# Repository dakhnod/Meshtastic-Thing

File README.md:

# Meshtastic-Thing

## Version 1/2

This board is a bit cleaner. It is composed of
- an esp32c3 super mini board
- an RFM95 board
- the PCB, as found in [the kicad folder](kicad/)

This PCB has two mino versions, with the second one labeled `v2`.
The first one connects `DIO0` with the ESP pin 8, which renders the built-in LED unusable.

The second version fixes this. Currently, the kicad Project contains the second version, but the variants.h file still uses GPIO8. You need to adjust this file if using the provided PCB.

Once I receive the second version and test it I will update this repository.

Steps:
1. Get an esp32c3 super mini board.
2. Get an RFM95 module
3. Solder up all boards as seen in the pictures
4. Clone the meshtastic firmware repo (recursively)
5. Open the repo firm VSCode with PlatformIO
6. Change out the file `variants/esp32c3/diy/esp32c3_super_mini/variant.h` to [the one](variants/esp32c3/diy/esp32c3_super_mini/variant.h) in this repo
7. If using the PCB from this repo, update the variants.h file to use pin 9 for DIO0
8. Build and flash the PlatformIO configuration `env:esp32c3_super_mini`
9. Check out [BLEnky](https://structure.nullco.de/?node_id=6622041d1a95fb4425f2323a&token=3c55f7bb1de0e79c9020dbb09deac741df56fc5474825407abb94f96714ce134) (unrelated, just wanted to advertise)
10. ???
11. Profit

## Version 0

Weird Meshtastic prototype I build.
For everyone wanting to replicate this (for reasons beyond me), here is some information.
Keep in mind that this instruction requires some skill level. If you have questions, open an issue!

Steps:
1. Get a Board like the one shown in the AliExpress listing (could also be black, doesn't matter. Open an issue if you're unsure)
2. Get an RFM95 module
3. Solder everything up according to the pictures (pin definition in [variant.h](variants/nrf52840/diy/nrf52_promicro_diy_xtal/variant.h))
4. Clone the meshtastic firmware repo (recursively)
5. Open the repo firm VSCode with PlatformIO
6. Change out the file `variants/nrf52840/diy/nrf52_promicro_diy_xtal/variant.h` to the one in this repo
7. Build and flash the PlatformIO configuration `env:nrf52_promicro_diy_xtal`
8. Check out [BLEnky](https://structure.nullco.de/?node_id=6622041d1a95fb4425f2323a&token=3c55f7bb1de0e79c9020dbb09deac741df56fc5474825407abb94f96714ce134) (unrelated, just wanted to advertise)
9. ???
10. Profit

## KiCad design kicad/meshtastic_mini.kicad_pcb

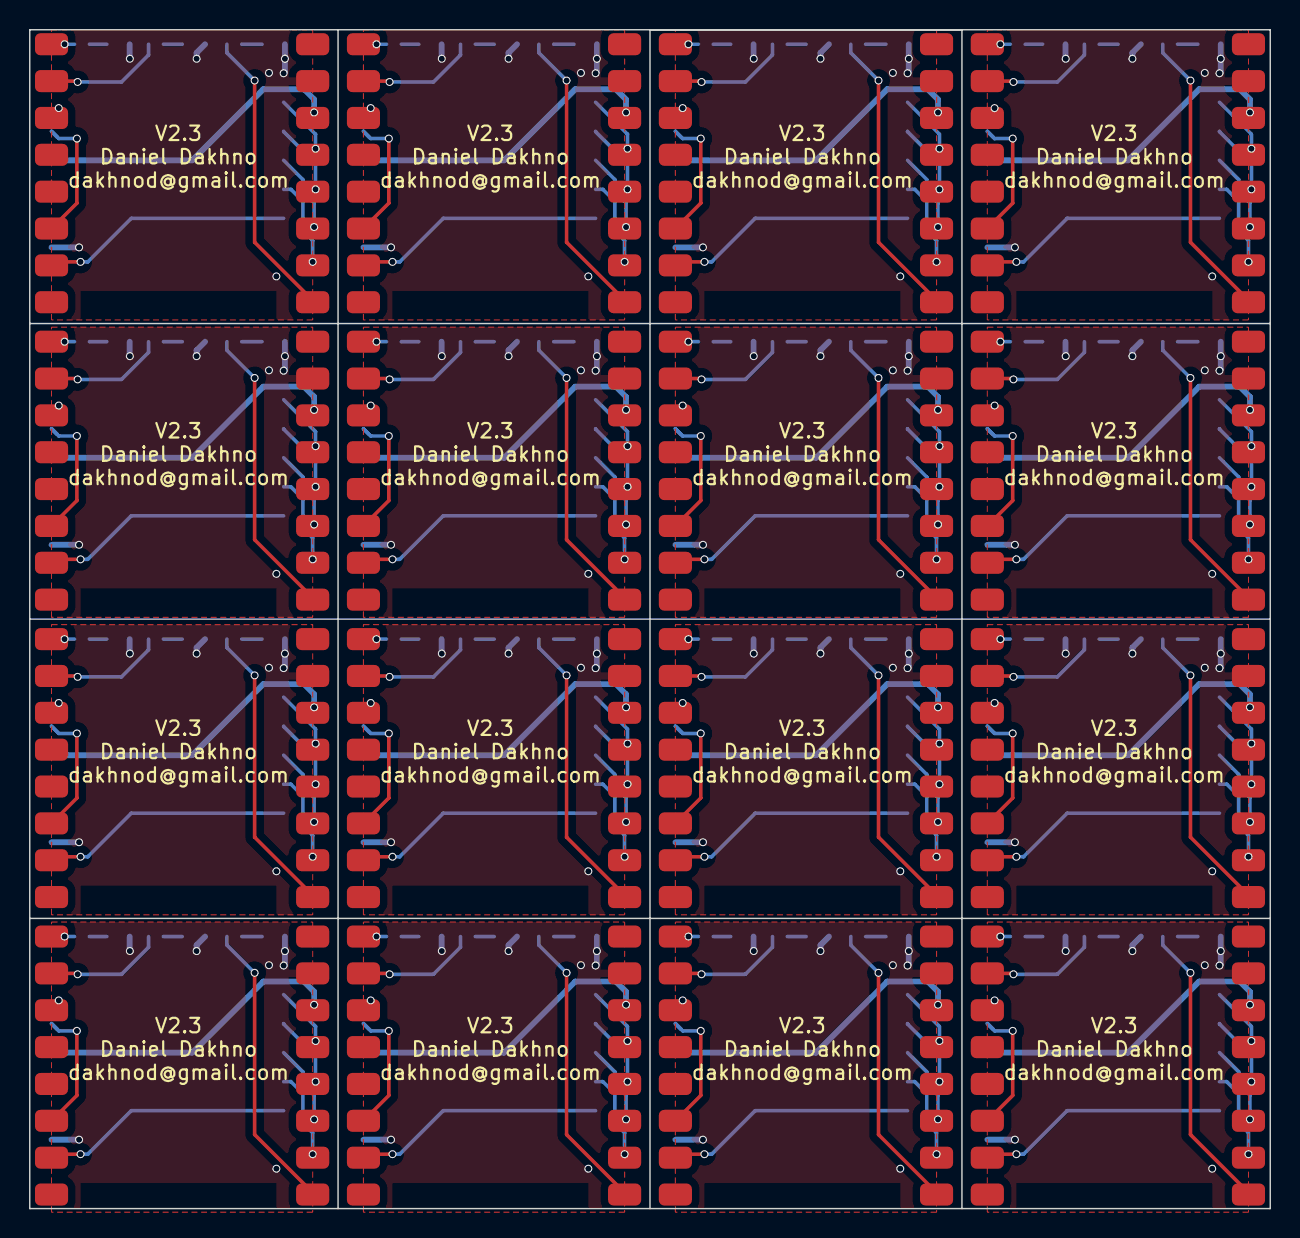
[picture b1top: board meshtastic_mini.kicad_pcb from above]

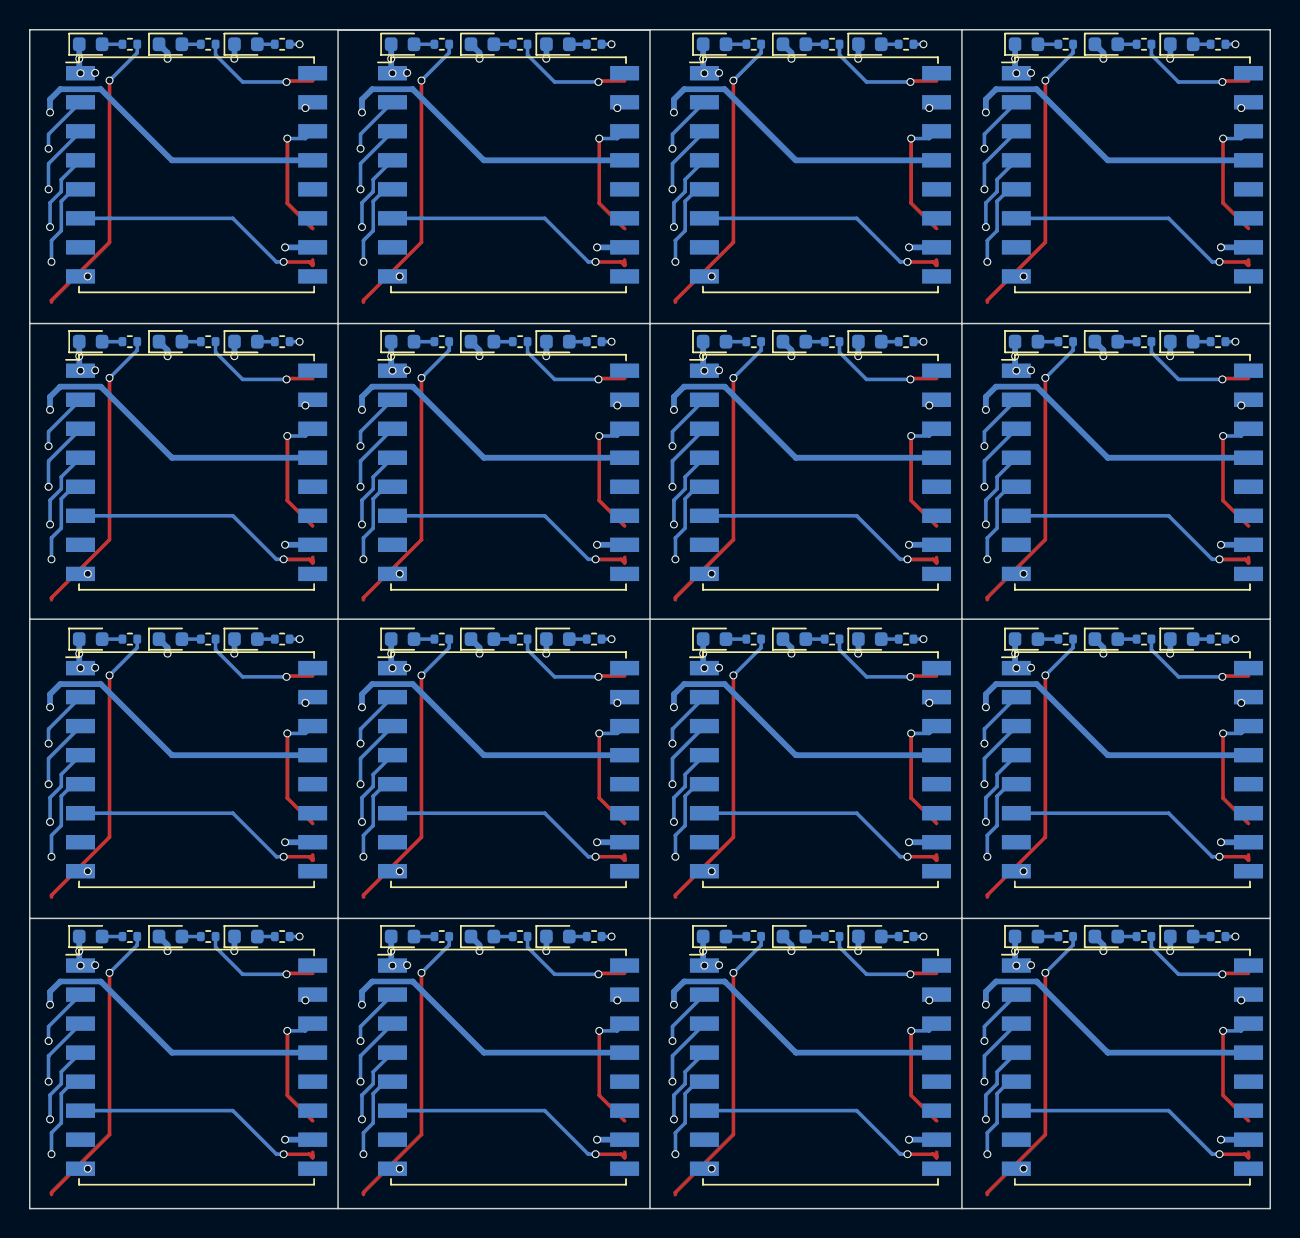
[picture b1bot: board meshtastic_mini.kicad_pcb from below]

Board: 2 copper layers, 85.5 x 81.2 mm, 128 parts (112 on the bottom side), 15 nets.

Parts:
D1, D2, D3, D4, D5, D6, D7, D8, D9, D10, D11, D12, D13, D14, D15, D16, D17, D18, D19, D20, D21, D22, D23, D24, D25, D26, D27, D28, D29, D30, D31, D32, D33, D34, D35, D36, D37, D38, D39, D40, D41, D42, D43, D44, D45, D46, D47, D48: LED; LED_0603_1608Metric
R1, R2, R3, R4, R5, R6, R7, R8, R9, R10, R11, R12, R13, R14, R15, R16, R17, R18, R19, R20, R21, R22, R23, R24, R25, R26, R27, R28, R29, R30, R31, R32, R33, R34, R35, R36, R37, R38, R39, R40, R41, R42, R43, R44, R45, R46, R47, R48: 1K; R_0402_1005Metric
U1, U3, U5, U7, U9, U11, U13, U15, U17, U19, U21, U23, U25, U27, U29, U31: ESP32-C3_SuperMini; ESP32-C3 SuperMini
U2, U4, U6, U8, U10, U12, U14, U16, U18, U20, U22, U24, U26, U28, U30, U32: RFM95W-868S2; HOPERF_RFM9XW_SMD

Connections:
+3.3V: U1.11 (3V3), U2.13 (3.3V), U3.11 (3V3), U4.13 (3.3V), U5.11 (3V3), U6.13 (3.3V), U7.11 (3V3), U8.13 (3.3V), U9.11 (3V3), U10.13 (3.3V), U11.11 (3V3), U12.13 (3.3V), U13.11 (3V3), U14.13 (3.3V), U15.11 (3V3), U16.13 (3.3V), U17.11 (3V3), U18.13 (3.3V), U19.11 (3V3), U20.13 (3.3V), U21.11 (3V3), U22.13 (3.3V), U23.11 (3V3), U24.13 (3.3V), U25.11 (3V3), U26.13 (3.3V), U27.11 (3V3), U28.13 (3.3V), U29.11 (3V3), U30.13 (3.3V), U31.11 (3V3), U32.13 (3.3V)
/DIO0: U1.6 (GPIO10), U2.14 (DIO0), U3.6 (GPIO10), U4.14 (DIO0), U5.6 (GPIO10), U6.14 (DIO0), U7.6 (GPIO10), U8.14 (DIO0), U9.6 (GPIO10), U10.14 (DIO0), U11.6 (GPIO10), U12.14 (DIO0), U13.6 (GPIO10), U14.14 (DIO0), U15.6 (GPIO10), U16.14 (DIO0), U17.6 (GPIO10), U18.14 (DIO0), U19.6 (GPIO10), U20.14 (DIO0), U21.6 (GPIO10), U22.14 (DIO0), U23.6 (GPIO10), U24.14 (DIO0), U25.6 (GPIO10), U26.14 (DIO0), U27.6 (GPIO10), U28.14 (DIO0), U29.6 (GPIO10), U30.14 (DIO0), U31.6 (GPIO10), U32.14 (DIO0)
/DIO1: U1.3 (GPIO7), U2.15 (DIO1), U3.3 (GPIO7), U4.15 (DIO1), U5.3 (GPIO7), U6.15 (DIO1), U7.3 (GPIO7), U8.15 (DIO1), U9.3 (GPIO7), U10.15 (DIO1), U11.3 (GPIO7), U12.15 (DIO1), U13.3 (GPIO7), U14.15 (DIO1), U15.3 (GPIO7), U16.15 (DIO1), U17.3 (GPIO7), U18.15 (DIO1), U19.3 (GPIO7), U20.15 (DIO1), U21.3 (GPIO7), U22.15 (DIO1), U23.3 (GPIO7), U24.15 (DIO1), U25.3 (GPIO7), U26.15 (DIO1), U27.3 (GPIO7), U28.15 (DIO1), U29.3 (GPIO7), U30.15 (DIO1), U31.3 (GPIO7), U32.15 (DIO1)
/RESET: U1.7 (GPIO20), U2.6 (RESET), U3.7 (GPIO20), U4.6 (RESET), U5.7 (GPIO20), U6.6 (RESET), U7.7 (GPIO20), U8.6 (RESET), U9.7 (GPIO20), U10.6 (RESET), U11.7 (GPIO20), U12.6 (RESET), U13.7 (GPIO20), U14.6 (RESET), U15.7 (GPIO20), U16.6 (RESET), U17.7 (GPIO20), U18.6 (RESET), U19.7 (GPIO20), U20.6 (RESET), U21.7 (GPIO20), U22.6 (RESET), U23.7 (GPIO20), U24.6 (RESET), U25.7 (GPIO20), U26.6 (RESET), U27.7 (GPIO20), U28.6 (RESET), U29.7 (GPIO20), U30.6 (RESET), U31.7 (GPIO20), U32.6 (RESET)
/SPI_MISO: U1.12 (GPIO4), U2.2 (MISO), U3.12 (GPIO4), U4.2 (MISO), U5.12 (GPIO4), U6.2 (MISO), U7.12 (GPIO4), U8.2 (MISO), U9.12 (GPIO4), U10.2 (MISO), U11.12 (GPIO4), U12.2 (MISO), U13.12 (GPIO4), U14.2 (MISO), U15.12 (GPIO4), U16.2 (MISO), U17.12 (GPIO4), U18.2 (MISO), U19.12 (GPIO4), U20.2 (MISO), U21.12 (GPIO4), U22.2 (MISO), U23.12 (GPIO4), U24.2 (MISO), U25.12 (GPIO4), U26.2 (MISO), U27.12 (GPIO4), U28.2 (MISO), U29.12 (GPIO4), U30.2 (MISO), U31.12 (GPIO4), U32.2 (MISO)
/SPI_MOSI: U1.13 (GPIO3), U2.3 (MOSI), U3.13 (GPIO3), U4.3 (MOSI), U5.13 (GPIO3), U6.3 (MOSI), U7.13 (GPIO3), U8.3 (MOSI), U9.13 (GPIO3), U10.3 (MOSI), U11.13 (GPIO3), U12.3 (MOSI), U13.13 (GPIO3), U14.3 (MOSI), U15.13 (GPIO3), U16.3 (MOSI), U17.13 (GPIO3), U18.3 (MOSI), U19.13 (GPIO3), U20.3 (MOSI), U21.13 (GPIO3), U22.3 (MOSI), U23.13 (GPIO3), U24.3 (MOSI), U25.13 (GPIO3), U26.3 (MOSI), U27.13 (GPIO3), U28.3 (MOSI), U29.13 (GPIO3), U30.3 (MOSI), U31.13 (GPIO3), U32.3 (MOSI)
/SPI_NSS: U1.15 (GPIO1), U2.5 (NSS), U3.15 (GPIO1), U4.5 (NSS), U5.15 (GPIO1), U6.5 (NSS), U7.15 (GPIO1), U8.5 (NSS), U9.15 (GPIO1), U10.5 (NSS), U11.15 (GPIO1), U12.5 (NSS), U13.15 (GPIO1), U14.5 (NSS), U15.15 (GPIO1), U16.5 (NSS), U17.15 (GPIO1), U18.5 (NSS), U19.15 (GPIO1), U20.5 (NSS), U21.15 (GPIO1), U22.5 (NSS), U23.15 (GPIO1), U24.5 (NSS), U25.15 (GPIO1), U26.5 (NSS), U27.15 (GPIO1), U28.5 (NSS), U29.15 (GPIO1), U30.5 (NSS), U31.15 (GPIO1), U32.5 (NSS)
/SPI_SCK: U1.14 (GPIO2), U2.4 (SCK), U3.14 (GPIO2), U4.4 (SCK), U5.14 (GPIO2), U6.4 (SCK), U7.14 (GPIO2), U8.4 (SCK), U9.14 (GPIO2), U10.4 (SCK), U11.14 (GPIO2), U12.4 (SCK), U13.14 (GPIO2), U14.4 (SCK), U15.14 (GPIO2), U16.4 (SCK), U17.14 (GPIO2), U18.4 (SCK), U19.14 (GPIO2), U20.4 (SCK), U21.14 (GPIO2), U22.4 (SCK), U23.14 (GPIO2), U24.4 (SCK), U25.14 (GPIO2), U26.4 (SCK), U27.14 (GPIO2), U28.4 (SCK), U29.14 (GPIO2), U30.4 (SCK), U31.14 (GPIO2), U32.4 (SCK)
GND: D1.1 (K), D2.1 (K), D3.1 (K), D4.1 (K), D5.1 (K), D6.1 (K), D7.1 (K), D8.1 (K), D9.1 (K), D10.1 (K), D11.1 (K), D12.1 (K), D13.1 (K), D14.1 (K), D15.1 (K), D16.1 (K), D17.1 (K), D18.1 (K), D19.1 (K), D20.1 (K), D21.1 (K), D22.1 (K), D23.1 (K), D24.1 (K), D25.1 (K), D26.1 (K), D27.1 (K), D28.1 (K), D29.1 (K), D30.1 (K), D31.1 (K), D32.1 (K), D33.1 (K), D34.1 (K), D35.1 (K), D36.1 (K), D37.1 (K), D38.1 (K), D39.1 (K), D40.1 (K), D41.1 (K), D42.1 (K), D43.1 (K), D44.1 (K), D45.1 (K), D46.1 (K), D47.1 (K), D48.1 (K), U1.10 (GND), U2.1 (GND), U2.8 (GND), U2.10 (GND), U3.10 (GND), U4.1 (GND), U4.8 (GND), U4.10 (GND), U5.10 (GND), U6.1 (GND), U6.8 (GND), U6.10 (GND), U7.10 (GND), U8.1 (GND), U8.8 (GND), U8.10 (GND), U9.10 (GND), U10.1 (GND), U10.8 (GND), U10.10 (GND), U11.10 (GND), U12.1 (GND), U12.8 (GND), U12.10 (GND), U13.10 (GND), U14.1 (GND), U14.8 (GND), U14.10 (GND), U15.10 (GND), U16.1 (GND), U16.8 (GND), U16.10 (GND), U17.10 (GND), U18.1 (GND), U18.8 (GND), U18.10 (GND), U19.10 (GND), U20.1 (GND), U20.8 (GND), U20.10 (GND), U21.10 (GND), U22.1 (GND), U22.8 (GND), U22.10 (GND), U23.10 (GND), U24.1 (GND), U24.8 (GND), U24.10 (GND), U25.10 (GND), U26.1 (GND), U26.8 (GND), U26.10 (GND), U27.10 (GND), U28.1 (GND), U28.8 (GND), U28.10 (GND), U29.10 (GND), U30.1 (GND), U30.8 (GND), U30.10 (GND), U31.10 (GND), U32.1 (GND), U32.8 (GND), U32.10 (GND)
unnamed: D1.2 (A), D4.2 (A), D7.2 (A), D10.2 (A), D13.2 (A), D16.2 (A), D19.2 (A), D22.2 (A), D25.2 (A), D28.2 (A), D31.2 (A), D34.2 (A), D37.2 (A), D40.2 (A), D43.2 (A), D46.2 (A), R1.2, R4.2, R7.2, R10.2, R13.2, R16.2, R19.2, R22.2, R25.2, R28.2, R31.2, R34.2, R37.2, R40.2, R43.2, R46.2
unnamed: D2.2 (A), D5.2 (A), D8.2 (A), D11.2 (A), D14.2 (A), D17.2 (A), D20.2 (A), D23.2 (A), D26.2 (A), D29.2 (A), D32.2 (A), D35.2 (A), D38.2 (A), D41.2 (A), D44.2 (A), D47.2 (A), R2.2, R5.2, R8.2, R11.2, R14.2, R17.2, R20.2, R23.2, R26.2, R29.2, R32.2, R35.2, R38.2, R41.2, R44.2, R47.2
unnamed: D3.2 (A), D6.2 (A), D9.2 (A), D12.2 (A), D15.2 (A), D18.2 (A), D21.2 (A), D24.2 (A), D27.2 (A), D30.2 (A), D33.2 (A), D36.2 (A), D39.2 (A), D42.2 (A), D45.2 (A), D48.2 (A), R3.2, R6.2, R9.2, R12.2, R15.2, R18.2, R21.2, R24.2, R27.2, R30.2, R33.2, R36.2, R39.2, R42.2, R45.2, R48.2
unnamed: R3.1, R6.1, R9.1, R12.1, R15.1, R18.1, R21.1, R24.1, R27.1, R30.1, R33.1, R36.1, R39.1, R42.1, R45.1, R48.1, U1.16 (GPIO0), U3.16 (GPIO0), U5.16 (GPIO0), U7.16 (GPIO0), U9.16 (GPIO0), U11.16 (GPIO0), U13.16 (GPIO0), U15.16 (GPIO0), U17.16 (GPIO0), U19.16 (GPIO0), U21.16 (GPIO0), U23.16 (GPIO0), U25.16 (GPIO0), U27.16 (GPIO0), U29.16 (GPIO0), U31.16 (GPIO0)
unnamed: R1.1, R4.1, R7.1, R10.1, R13.1, R16.1, R19.1, R22.1, R25.1, R28.1, R31.1, R34.1, R37.1, R40.1, R43.1, R46.1, U1.1 (GPIO5), U3.1 (GPIO5), U5.1 (GPIO5), U7.1 (GPIO5), U9.1 (GPIO5), U11.1 (GPIO5), U13.1 (GPIO5), U15.1 (GPIO5), U17.1 (GPIO5), U19.1 (GPIO5), U21.1 (GPIO5), U23.1 (GPIO5), U25.1 (GPIO5), U27.1 (GPIO5), U29.1 (GPIO5), U31.1 (GPIO5)
unnamed: R2.1, R5.1, R8.1, R11.1, R14.1, R17.1, R20.1, R23.1, R26.1, R29.1, R32.1, R35.1, R38.1, R41.1, R44.1, R47.1, U1.2 (GPIO6), U3.2 (GPIO6), U5.2 (GPIO6), U7.2 (GPIO6), U9.2 (GPIO6), U11.2 (GPIO6), U13.2 (GPIO6), U15.2 (GPIO6), U17.2 (GPIO6), U19.2 (GPIO6), U21.2 (GPIO6), U23.2 (GPIO6), U25.2 (GPIO6), U27.2 (GPIO6), U29.2 (GPIO6), U31.2 (GPIO6)

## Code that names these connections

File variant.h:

#ifndef _VARIANT_PROMICRO_DIY_
#define _VARIANT_PROMICRO_DIY_

/** Master clock frequency */
#define VARIANT_MCK (64000000ul)

#define USE_LFXO // Board uses 32khz crystal for LF
// #define USE_LFRC // Board uses RC for LF

#define PROMICRO_DIY_XTAL
/*----------------------------------------------------------------------------
 *        Headers
 *----------------------------------------------------------------------------*/

#include "WVariant.h"

#ifdef __cplusplus
extern "C"
{
#endif // __cplusplus

// Number of pins defined in PinDescription array
#define PINS_COUNT (48)
#define NUM_DIGITAL_PINS (48)
#define NUM_ANALOG_INPUTS (0)
#define NUM_ANALOG_OUTPUTS (0)

// Pin 13 enables 3.3V periphery. If the Lora module is on this pin, then it should stay enabled at all times.
#define PIN_3V3_EN (0 + 13) // P0.13

    // WIRE IC AND IIC PINS
    // #define WIRE_INTERFACES_COUNT 1

#define MESHTASTIC_EXCLUDE_GPS 1
#define MESHTASTIC_EXCLUDE_SCREEN 1

#define WIRE_INTERFACES_COUNT 1

#define PIN_WIRE_SDA (32 + 4) // P1.04
#define PIN_WIRE_SCL (0 + 11) // P0.11

// LED
#define PIN_LED1 (0 + 15) // P0.15
#define LED_BUILTIN PIN_LED1
// Actually red
#define LED_BLUE PIN_LED1
#define LED_STATE_ON 1 // State when LED is lit

// UART interfaces
#define PIN_SERIAL1_RX (32 + 0)
#define PIN_SERIAL1_TX (32 + 24)

#define PIN_SERIAL2_RX (0 + 29)
#define PIN_SERIAL2_TX (0 + 31)

// Serial interfaces
#define SPI_INTERFACES_COUNT 1

#define PIN_SPI_MISO (0 + 2)   // P0.02
#define PIN_SPI_MOSI (32 + 15) // P1.15
#define PIN_SPI_SCK (32 + 13)  // P1.11

#define LORA_CS (32 + 11)
#define LORA_RESET (0 + 10)

#define USE_RF95

#define LORA_DIO1 (0 + 22)
#define LORA_DIO0 (0 + 24)

#ifdef __cplusplus
}
#endif

/*----------------------------------------------------------------------------
 *        Arduino objects - C++ only
 *----------------------------------------------------------------------------*/

#endif

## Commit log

2025-11-08 Enhance README with replication instructions and images
    Expanded instructions for replicating the Meshtastic prototype, including detailed steps and images.
2025-11-08 Clarify skill level required for instructions
    Added a note about required skill level for instructions.
2025-12-12 updated instructions for new board
2025-12-12 Update README with version and images
    Updated version number and added images to README.
2025-12-12 added kicad files
2025-12-12 added JLCPCB zip
2025-12-16 connected DIO0 to pin 10 instead of 9
2025-12-27 fixed third LED wiring (that noone will probably ever use)
2025-12-27 adapted for usage with XIAO nrf52 module
